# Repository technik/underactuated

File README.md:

# underactuated
Stuff related to the underactuated robotics class

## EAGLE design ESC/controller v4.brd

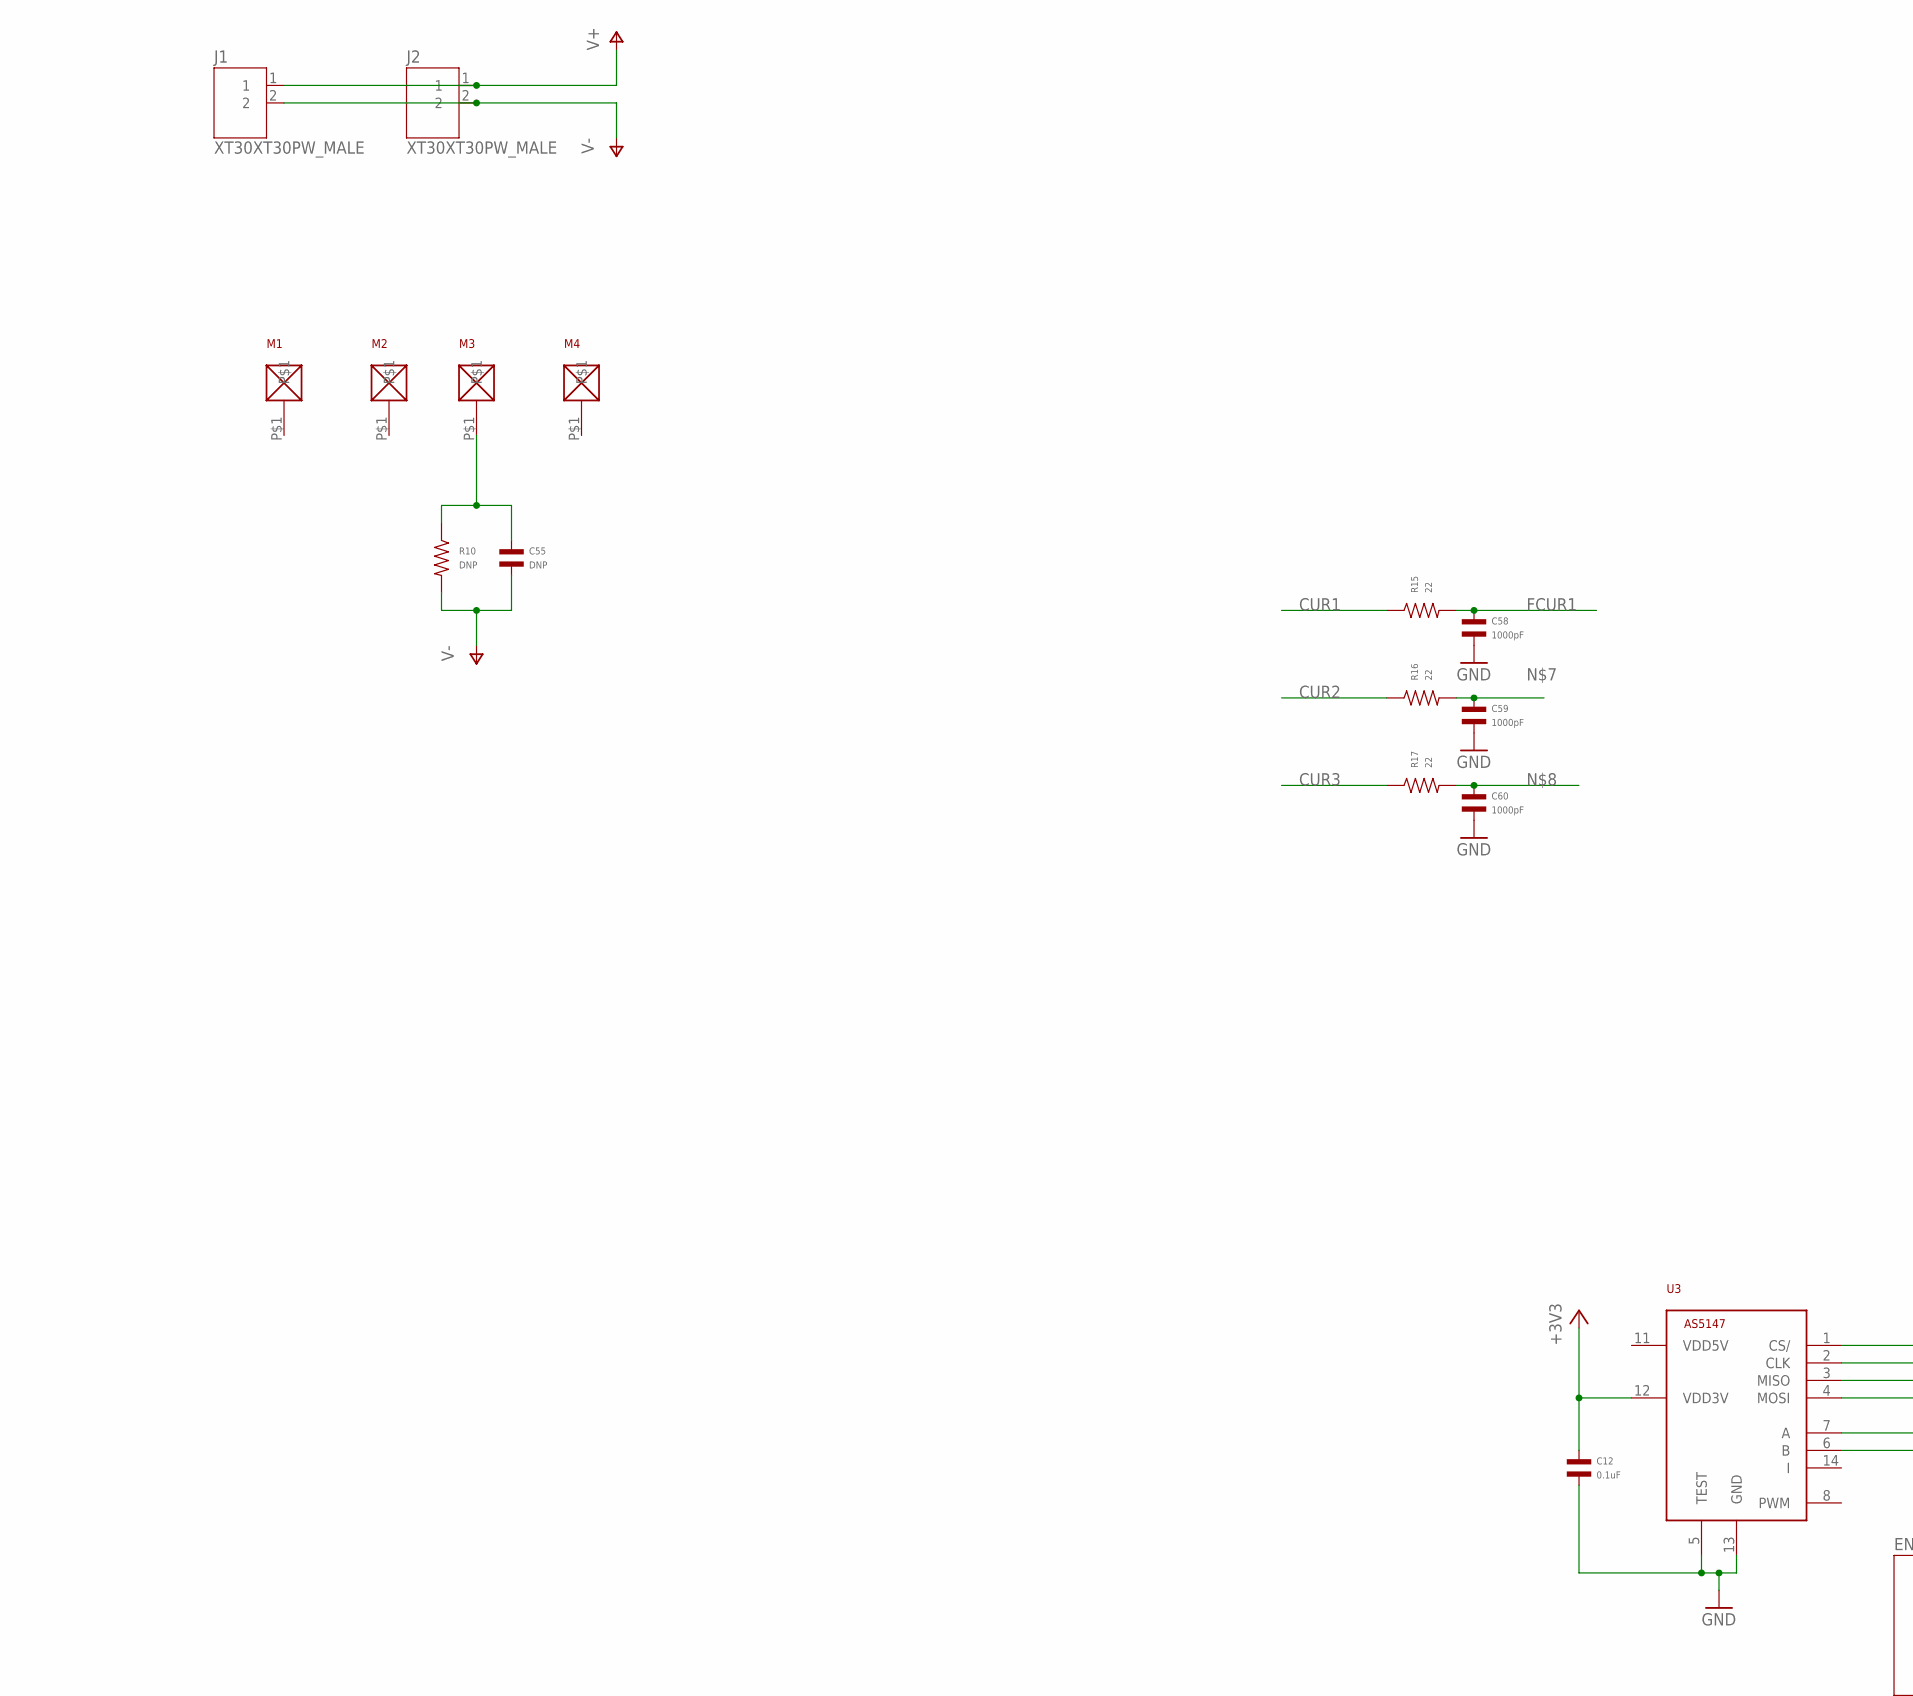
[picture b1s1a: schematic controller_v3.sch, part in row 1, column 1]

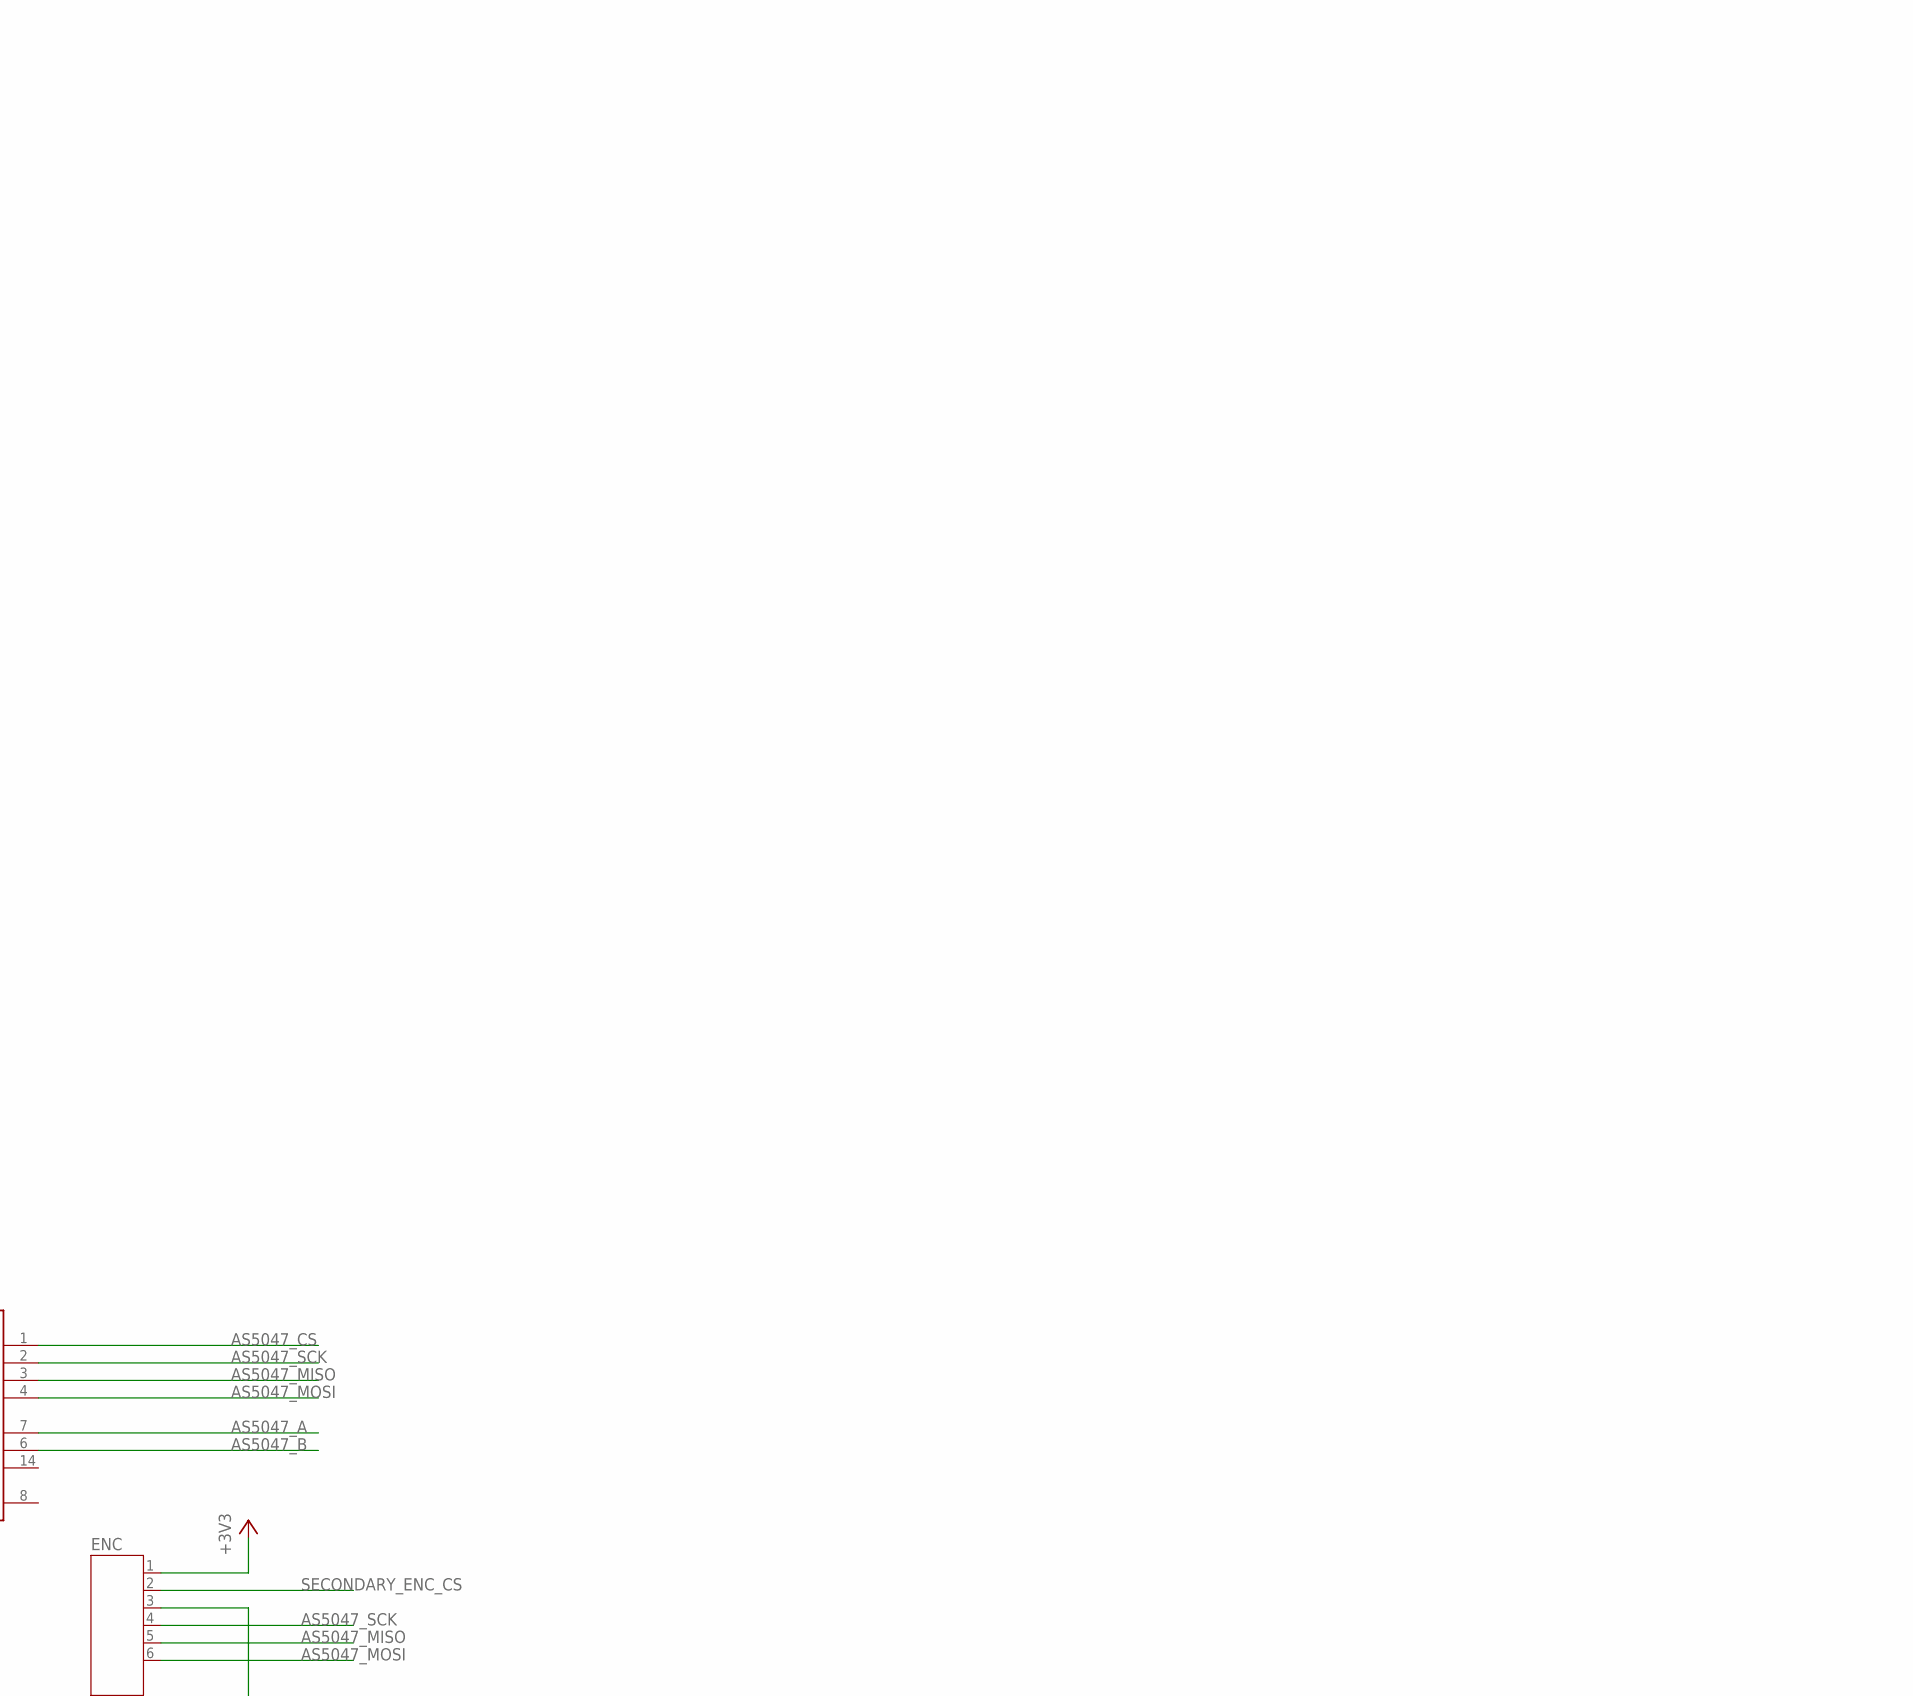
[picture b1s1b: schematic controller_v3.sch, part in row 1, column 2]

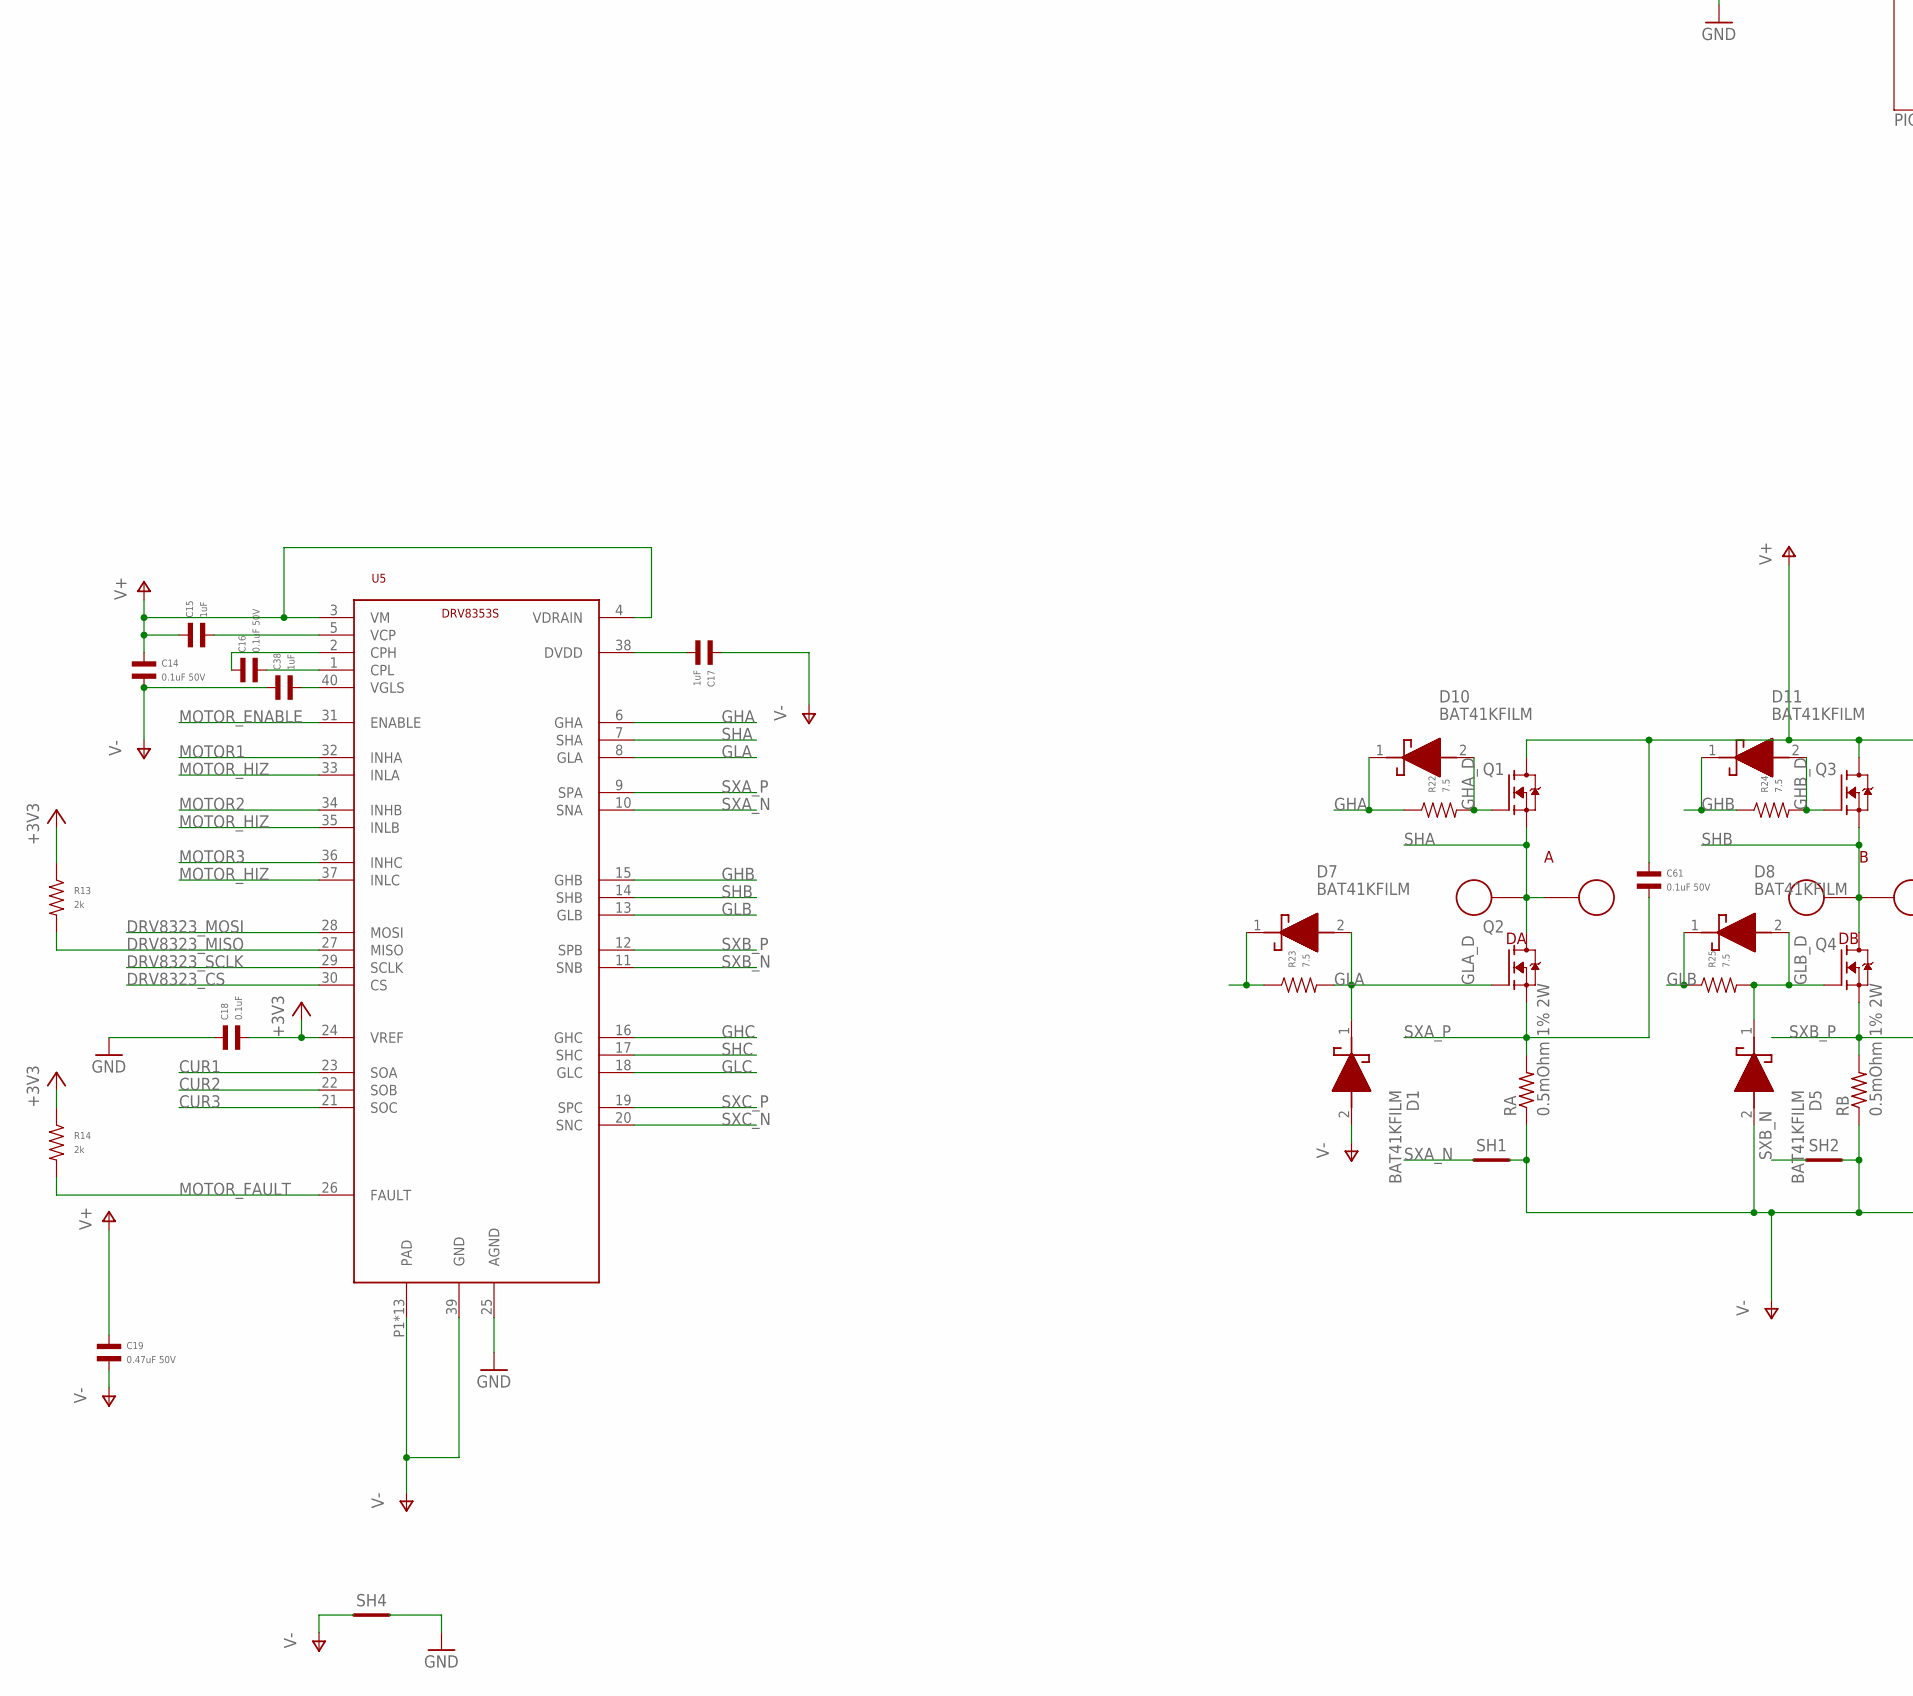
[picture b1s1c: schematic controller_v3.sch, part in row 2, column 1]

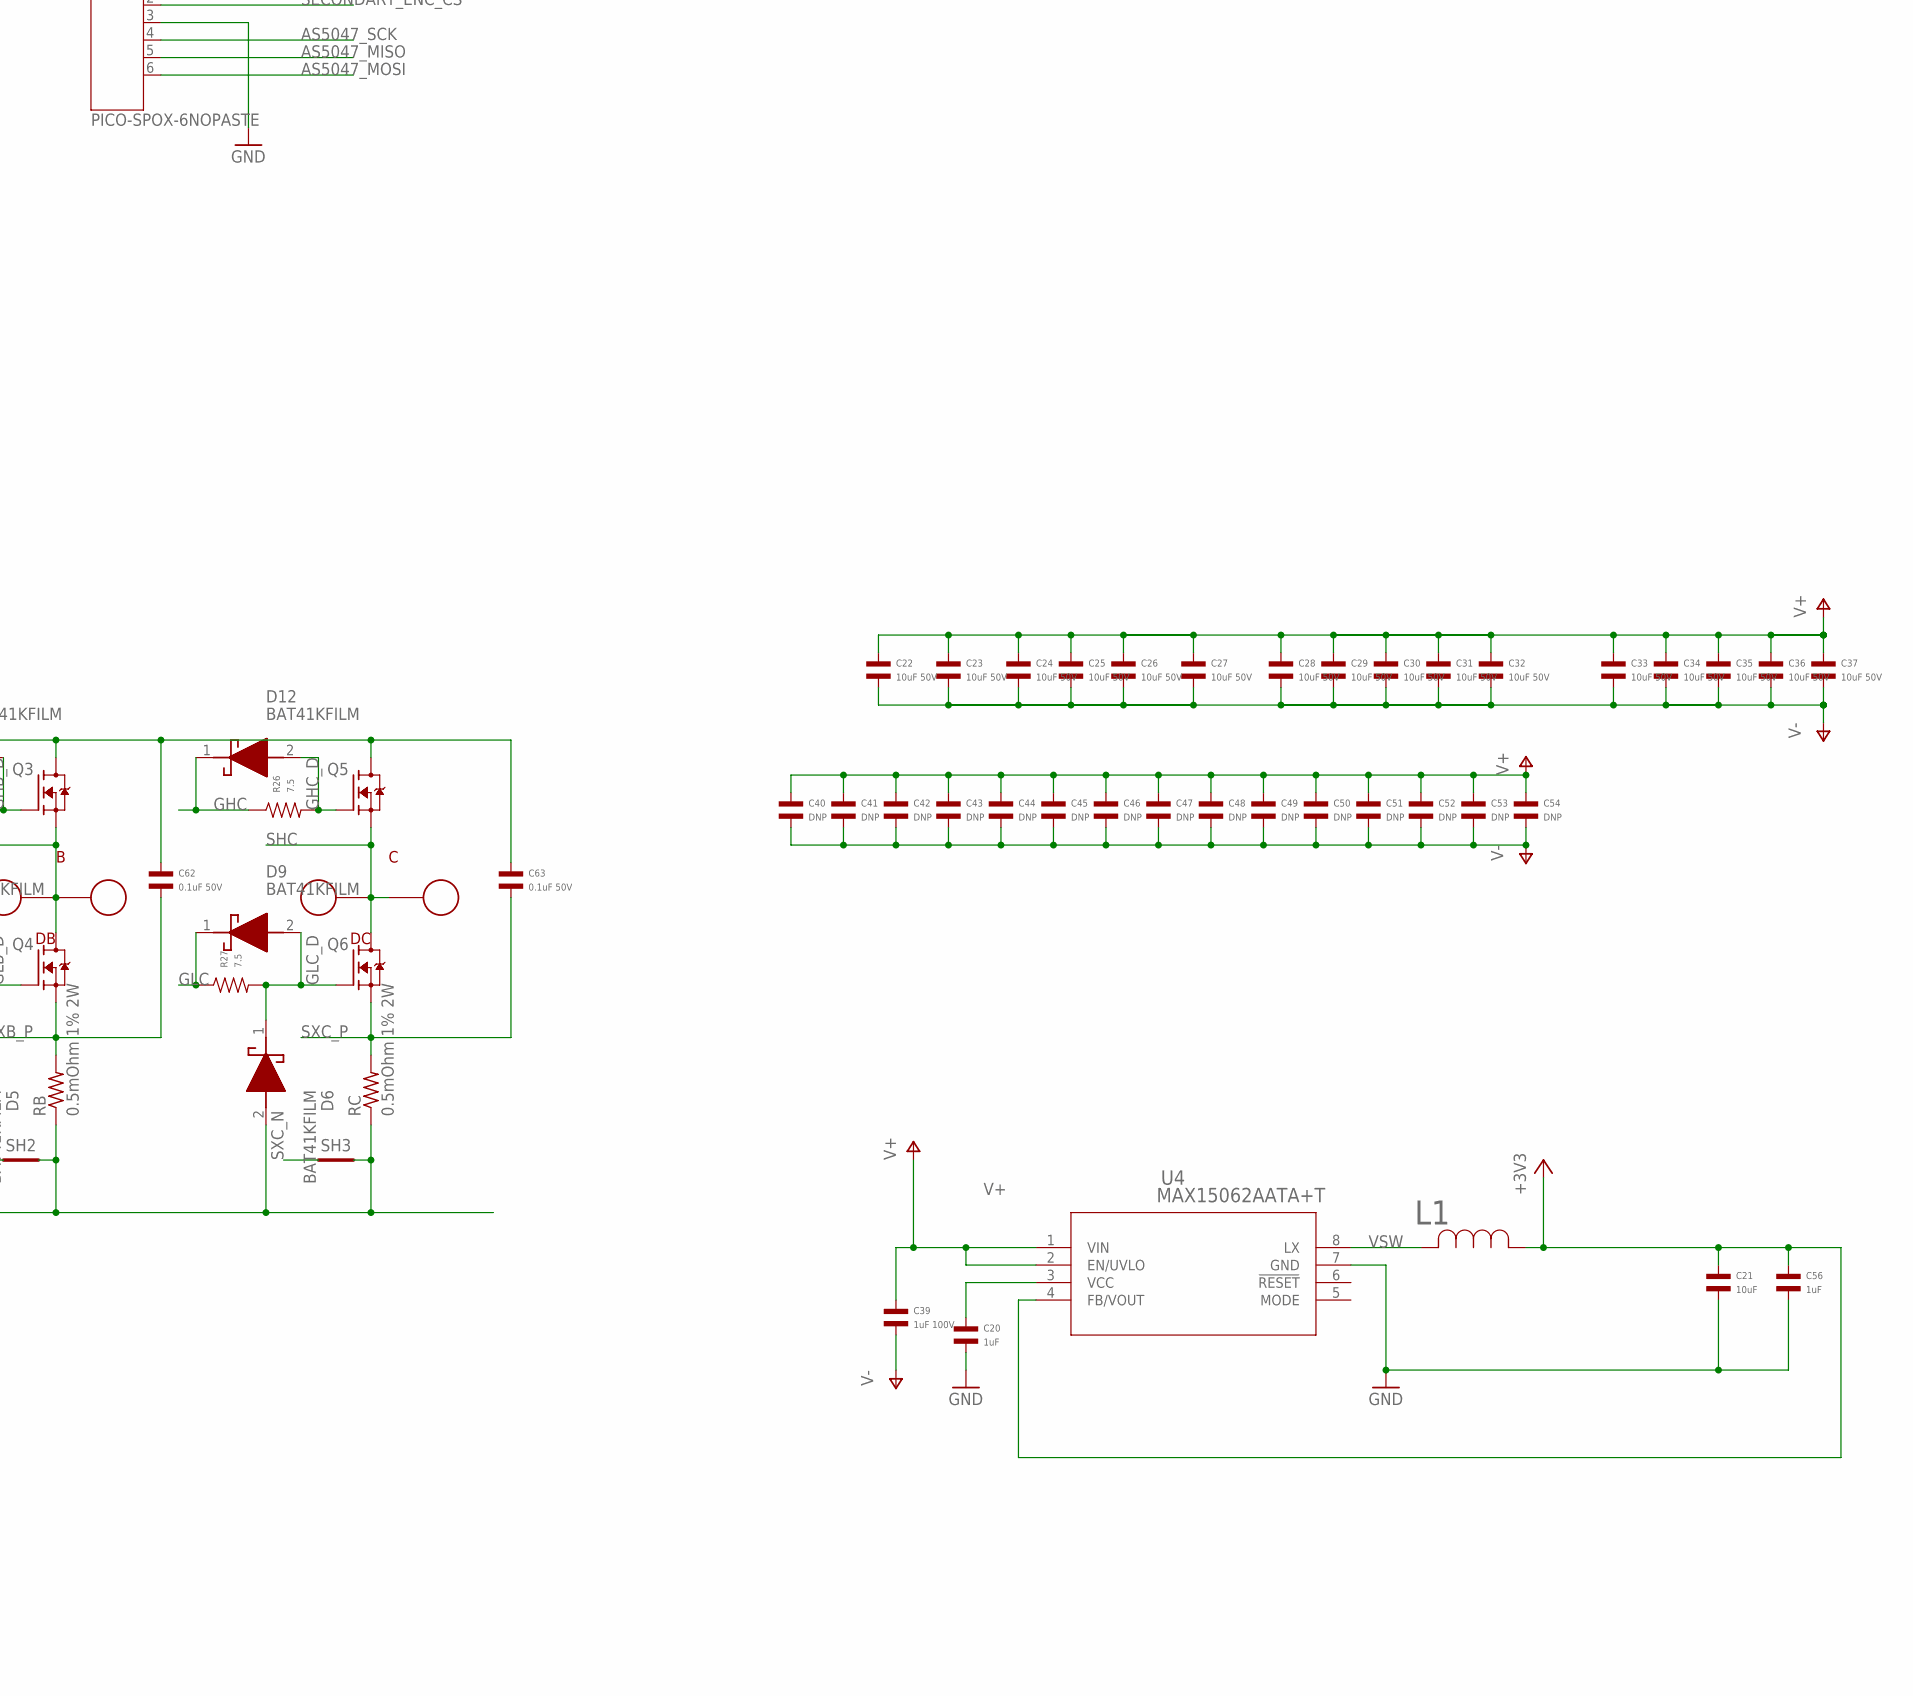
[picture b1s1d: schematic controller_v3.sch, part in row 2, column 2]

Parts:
A: PAD16AWG_PAD; 16AWG_PAD
B: PAD16AWG_PAD; 16AWG_PAD
C: PAD16AWG_PAD; 16AWG_PAD
C12, C18: 0.1uF; C0402; MPN MF-CAP-0402-0.1uF
C14, C16: 0.1uF 50V; C0402; MPN CGA2B3X7R1H104K050BB
C15, C17, C56: 1uF; C0402; MPN MF-CAP-0402-1uF
C19: 0.47uF 50V; C0402; MPN GRM155R61H474KE11D
C20: 1uF; C0603; MPN MF-CAP-0603-1uF
C21: 10uF; C1206; MPN MF-CAP-1206-10uF
C22, C23, C24, C25, C26, C27, C28, C29, C30, C31, C32, C33, C34, C36, C37: 10uF 50V; C1206; MPN C3216X7R1H106K160AE
C35: 10uF 50V; C1206_NOBORDER; MPN C3216X7R1H106K160AE
C38: 1uF; C0603; MPN C1608X7R1E105K080AE
C39: 1uF 100V; C0805; MPN GCM21BC72A105KE36L
C40, C41, C42, C43, C44, C45, C46, C47, C48, C49, C50, C51, C52, C53, C54: DNP; C1206_NOCREAM
C55: DNP; C0402
C58, C59, C60: 1000pF; C0402_NOBORDER; MPN MF-CAP-0402-1nF
C61, C63: 0.1uF 50V; C1206; MPN 12065C104KAZ2A
C62: 0.1uF 50V; C0603_NOBORDER; MPN 06035C104KAZ2A
D1, D5, D6, D7, D8, D9, D10, D11, D12: BAT41KFILM; SODFL1608X70N; MPN BAT41KFILM
DA: PAD24AWG_PAD; 24AWG_PAD
DB: PAD24AWG_PAD; 24AWG_PAD
DC: PAD24AWG_PAD; 24AWG_PAD
ENC: PICO-SPOX-6NOPASTE; PICO-SPOX-SMT-RA-6-NOPASTE
J1, J2: XT30XT30PW_MALE; XT30PW_MALE
L1: SRN4018-220M; IND_BOURNS_SRN4018; MANUFACTURER_PART_NUMBER SRN4018-330M
M1, M2, M3, M4: MOUNT; M2.5MOUNT
Q1, Q2, Q3, Q4, Q5, Q6: TPH1R204PLSOP_ADVANCE_8; SOP_ADVANCE_8; MPN TPH2R506PL,L1Q
R10: DNP; R0402
R13, R14: 2k; R0402; MPN MF-RES-0402-2K
R15, R16, R17: 22; R0402_NOBORDER; MPN MF-RES-0402-22
R22, R23, R24, R25, R26, R27: 7.5; R0402; MPN RC0402FR-077R5L
RA: 0.5mOhm 1% 2W; M1206; MPN HCS1206FTL500
RB: 0.5mOhm 1% 2W; M1206; MPN HCS1206FTL500
RC: 0.5mOhm 1% 2W; M1206; MPN HCS1206FTL500
SH1, SH2, SH3: SHORTT5; SHORT_TOP-50
SH4: SHORTMEDIUM; SHORT_TOP-MEDIUM
U3: AS5147; TSSOP14; MPN AS5047P-ATSM
U4: MAX15062AATA+T; 21-0487A_MXM; MPN MAX15062AATA+T
U5: DRV8353S; WQFN-40; MPN DRV8353FSRTAR

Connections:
+3V3: C12.P$1, C18.P$2, C21.P$1, C56.P$1, ENC.1, L1.1, R13.P$1, R14.P$1, U3.12 (VDD3V), U4.4 (FB/VOUT), U5.24 (VREF)
AS5047_A: U3.7 (A)
AS5047_B: U3.6 (B)
AS5047_CS: U3.1 (CS/)
AS5047_MISO: ENC.5, U3.3 (MISO)
AS5047_MOSI: ENC.6, U3.4 (MOSI)
AS5047_SCK: ENC.4, U3.2 (CLK)
CUR1: R15.P$1, U5.23 (SOA)
CUR2: R16.P$1, U5.22 (SOB)
CUR3: R17.P$1, U5.21 (SOC)
DRV8323_CS: U5.30 (CS)
DRV8323_MISO: R13.P$2, U5.27 (MISO)
DRV8323_MOSI: U5.28 (MOSI)
DRV8323_SCLK: U5.29 (SCLK)
FCUR1: C58.P$1, R15.P$2
GHA: D10.1 (K), R22.P$1, U5.6 (GHA)
GHA_D: D10.2 (A), Q1.4 (G), R22.P$2
GHB: D11.1 (K), R24.P$1, U5.15 (GHB)
GHB_D: D11.2 (A), Q3.4 (G), R24.P$2
GHC: D12.1 (K), R26.P$1, U5.16 (GHC)
GHC_D: D12.2 (A), Q5.4 (G), R26.P$2
GLA: D7.1 (K), R23.P$1, U5.8 (GLA)
GLA_D: D1.1 (K), D7.2 (A), Q2.4 (G), R23.P$2
GLB: D8.1 (K), R25.P$1, U5.13 (GLB)
GLB_D: D5.1 (K), D8.2 (A), Q4.4 (G), R25.P$2
GLC: D9.1 (K), R27.P$1, U5.18 (GLC)
GLC_D: D6.1 (K), D9.2 (A), Q6.4 (G), R27.P$2
GND: C12.P$2, C18.P$1, C20.P$2, C21.P$2, C56.P$2, C58.P$2, C59.P$2, C60.P$2, ENC.3, SH4.2, U3.5 (TEST), U3.13 (GND), U4.7 (GND), U5.25 (AGND)
MOTOR1: U5.32 (INHA)
MOTOR2: U5.34 (INHB)
MOTOR3: U5.36 (INHC)
MOTOR_ENABLE: U5.31 (ENABLE)
MOTOR_FAULT: R14.P$2, U5.26 (FAULT)
MOTOR_HIZ: U5.33 (INLA), U5.35 (INLB), U5.37 (INLC)
unnamed: C55.P$1, M3.P$1, R10.P$1
unnamed: C38.P$2, U5.40 (VGLS)
unnamed: C20.P$1, U4.3 (VCC)
unnamed: C59.P$1, R16.P$2
unnamed: C60.P$1, R17.P$2
unnamed: C16.P$2, U5.1 (CPL)
unnamed: C16.P$1, U5.2 (CPH)
unnamed: C15.P$2, U5.5 (VCP)
unnamed: C17.P$2, U5.38 (DVDD)
SECONDARY_ENC_CS: ENC.2
SHA: A.1, DA.P$1, Q1.1 (S), Q1.2 (S), Q1.3 (S), Q2.5 (D), Q2.6 (D), Q2.7 (D), Q2.8 (D), Q2.PAD (D), U5.7 (SHA)
SHB: B.1, DB.P$1, Q3.1 (S), Q3.2 (S), Q3.3 (S), Q4.5 (D), Q4.6 (D), Q4.7 (D), Q4.8 (D), Q4.PAD (D), U5.14 (SHB)
SHC: C.1, DC.P$1, Q5.1 (S), Q5.2 (S), Q5.3 (S), Q6.5 (D), Q6.6 (D), Q6.7 (D), Q6.8 (D), Q6.PAD (D), U5.17 (SHC)
SXA_N: SH1.1, U5.10 (SNA)
SXA_P: C61.P$2, Q2.1 (S), Q2.2 (S), Q2.3 (S), RA.2, U5.9 (SPA)
SXB_N: SH2.1, U5.11 (SNB)
SXB_P: C62.P$2, Q4.1 (S), Q4.2 (S), Q4.3 (S), RB.2, U5.12 (SPB)
SXC_N: SH3.1, U5.20 (SNC)
SXC_P: C63.P$2, Q6.1 (S), Q6.2 (S), Q6.3 (S), RC.2, U5.19 (SPC)
V+: C14.P$1, C15.P$1, C19.P$1, C22.P$1, C23.P$1, C24.P$1, C25.P$1, C26.P$1, C27.P$1, C28.P$1, C29.P$1, C30.P$1, C31.P$1, C32.P$1, C33.P$1, C34.P$1, C35.P$1, C36.P$1, C37.P$1, C39.P$1, C40.P$1, C41.P$1, C42.P$1, C43.P$1, C44.P$1, C45.P$1, C46.P$1, C47.P$1, C48.P$1, C49.P$1, C50.P$1, C51.P$1, C52.P$1, C53.P$1, C54.P$1, C61.P$1, C62.P$1, C63.P$1, J1.1, J2.1, Q1.5 (D), Q1.6 (D), Q1.7 (D), Q1.8 (D), Q1.PAD (D), Q3.5 (D), Q3.6 (D), Q3.7 (D), Q3.8 (D), Q3.PAD (D), Q5.5 (D), Q5.6 (D), Q5.7 (D), Q5.8 (D), Q5.PAD (D), U4.1 (VIN), U4.2 (EN/UVLO), U5.3 (VM), U5.4 (VDRAIN)
V-: C14.P$2, C17.P$1, C19.P$2, C22.P$2, C23.P$2, C24.P$2, C25.P$2, C26.P$2, C27.P$2, C28.P$2, C29.P$2, C30.P$2, C31.P$2, C32.P$2, C33.P$2, C34.P$2, C35.P$2, C36.P$2, C37.P$2, C38.P$1, C39.P$2, C40.P$2, C41.P$2, C42.P$2, C43.P$2, C44.P$2, C45.P$2, C46.P$2, C47.P$2, C48.P$2, C49.P$2, C50.P$2, C51.P$2, C52.P$2, C53.P$2, C54.P$2, C55.P$2, D1.2 (A), D5.2 (A), D6.2 (A), J1.2, J2.2, R10.P$2, RA.1, RB.1, RC.1, SH1.2, SH2.2, SH3.2, SH4.1, U5.39 (GND), U5.P1 (PAD), U5.P2 (PAD), U5.P3 (PAD), U5.P7 (PAD), U5.P8 (PAD), U5.P9 (PAD), U5.P12 (PAD), U5.P13 (PAD), U5.P14 (PAD), U5.P17 (PAD), U5.P18 (PAD), U5.P19 (PAD), U5.PAD
VSW: L1.2, U4.8 (LX)

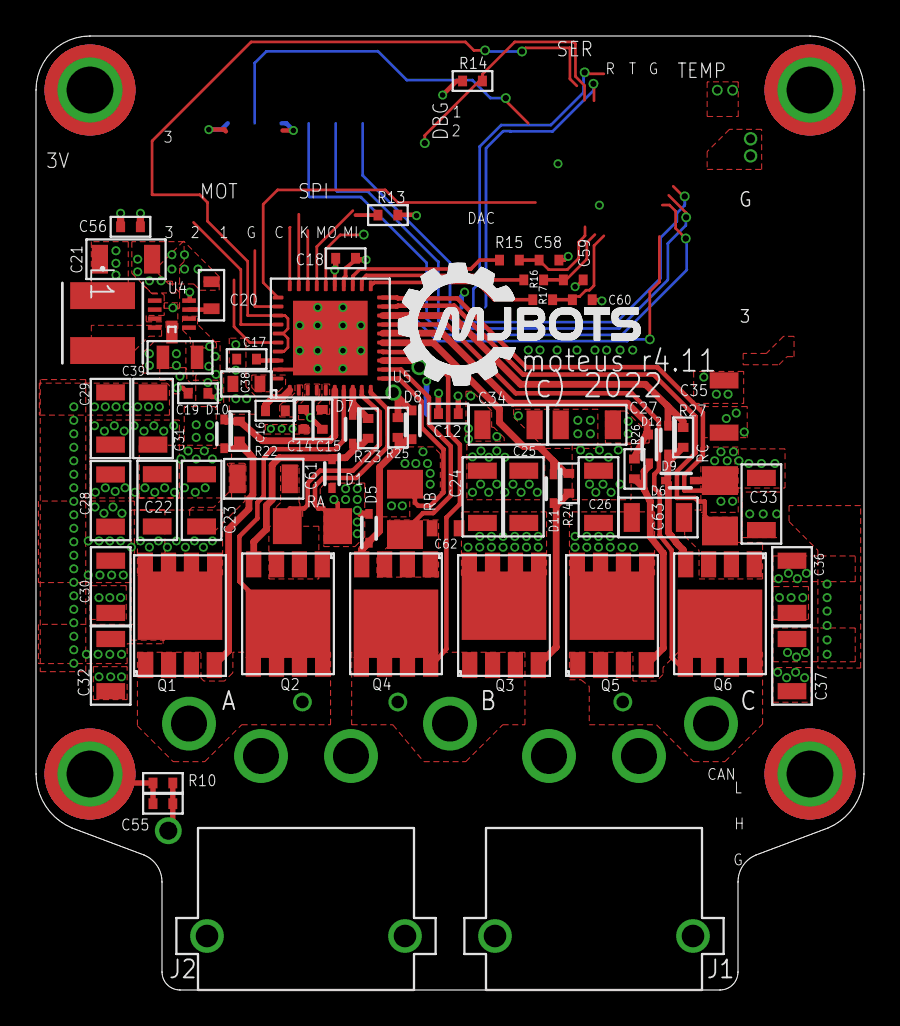
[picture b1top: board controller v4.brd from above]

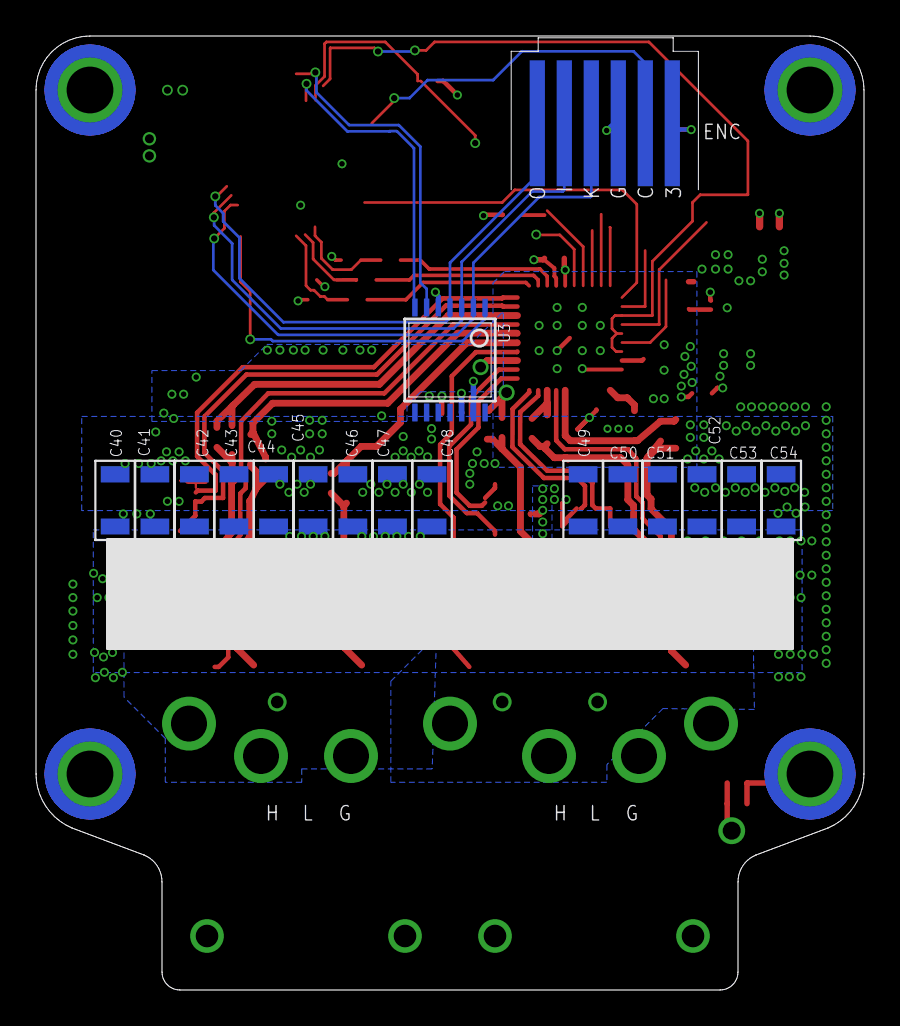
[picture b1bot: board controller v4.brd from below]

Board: 4 copper layers, 46.0 x 53.0 mm, 101 parts (17 on the bottom side), 45 nets.

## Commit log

2019-07-04 RobotHAL project
2019-07-04 Pendulum simulation
2023-02-18 Reorganize files and added an ImGui pendulum app
2023-02-18 Basic pendulum simulation
2023-02-18 Fixed numerical unstability
2023-02-18 randomize configurations
2023-02-18 Comment clean up
2023-02-18 better UI
2023-02-19 Energy pump controller for pendulum
2023-02-19 Setup acrobot project
2023-02-19 Acrobot: Use relative angles for the elbow.
2023-02-19 Mat22 implementation and WIP acrobot model
2023-02-20 WIP: Pendulum value iteration policy.
2023-02-25 WIP pendulum LQR and some more math ops
2023-02-25 Added dynamixel bridge project
2023-02-26 Add catkin workspace
2023-02-26 Update gitignore for ROS
2023-02-26 Fix CMake symlink
2023-02-26 Update CMake
2023-02-26 Add pendulum catkin pkg
2023-02-26 WIP Dynamixel bridge
2023-02-26 ROS skeleton of controller
2023-02-26 Upgrade to c++17
2023-02-26 Controller running in the controller node
2023-02-26 Controller in node (#1)
    * ROS skeleton of controller
    * Upgrade to c++17
    * Controller running in the controller node
2023-02-26 LED toggle and WIP reading from PC
2023-02-26 Add Pendulum urdf and rviz launch files
2023-02-26 pass on dynamixel bridge
2023-02-26 Refactor: Make a folder for each node in the pendulum package
2023-02-27 WIP pendulum sim node
2023-03-01 Uncomment simulation
2023-03-01 Remove devel
2023-03-01 pendulum simulator subscibes to the control topic.
2023-03-01 Added serial port library for linux
2023-03-07 4th order Runge-Kutta simulation
2023-03-07 Add control input subscriber
2023-03-08 Add matplotlib-based visualizer
2023-03-08 Add PD to controller
2023-03-08 Cleanup
2023-03-08 Add energy plot
2023-03-09 Fix typo g=9.18 🙄
2023-03-09 remove const value param
2023-03-09 HAL Updates
2023-03-09 Add ros_lib
2023-03-11 Clean up build folder (shouldn't be tracked)
2023-03-11 Multiplatform implementation of serial port
2023-03-11 Hal serial port (#5)
    * Added serial port library for linux
    * Clean up build folder (shouldn't be tracked)
    * Multiplatform implementation of serial port
2023-03-11 Dynamixel writes
2023-03-12 WIP: Extending dynamixel functionality
2023-03-13 wip hal
2023-03-13 wip read data from ax12
2023-03-13 Build fix
2023-03-13 Ping dynamixel AX12
2023-03-24 Arduino motor controller
2023-03-25 Working?
2023-03-25 WORKING!
2023-03-25 Cleanup prints
2023-03-26 Improved half bridge dynamixel control
2023-03-27 Refactoring
2023-03-27 Working bang-bang energy shaping controll
2023-03-27 Fix date
2023-04-08 Hopper v2 test code
2023-04-08 bldc motor moves in both directions
2023-04-09 First version of Field oriented Control
2023-04-10 Faster trapezoidal control
2023-05-24 Hopper cube local changes
2023-06-01 Add a micromouse project and share some code
2023-06-30 Add clean ESC
2023-09-23 rattrap gyro
2023-09-27 WIP: Test code for esc_v5
2023-10-02 working h-bridge on the esc
2023-10-02 Added a segway model using the Arduino framework on the stm32 nucleo F446re
2023-10-02 clean code and add a can library to the project
2023-10-17 missing segway code
2023-10-18 Wheeled pendulum EoM
2023-10-19 Wheeled pendulum EoM (#7)
2023-10-22 Segway project: WIP rigid body simulation
2023-10-22 Moved rendering into a presentation class
2023-10-23 circle to circle collision detection
2023-10-23 Introducing AABBs
2023-10-23 circle to box intersection
2023-10-27 force generators
2023-10-27 support kinematic bodies
2023-10-28 Basic pivot constraint
2023-10-28 WIP: Big matrix for the constraint solver
2023-10-29 Removed custom matrix code
2023-11-20 RK4 Segway simulator
2024-02-27 EKF in python
2024-03-10 Noisy signal EKF test
2024-03-16 copied pendulum mode into a new project folder
2024-03-16 Differential cart model
2024-03-17 cart simulation
2024-03-17 added eigen and implemented a linear actuation policy
2024-03-17 add a timeout
2024-03-17 Compute a score for each run
2024-03-17 WIP training
2024-03-17 Training works on debug, but not release
2024-03-17 fix stack corruption that was breaking training.
2024-03-17 update default training configuration.
2024-03-18 Draw network activations
2024-03-21 multilayer perceptron working
2024-03-21 local search training
2024-03-21 policy now controls motor velocity directly (simplified problem).
2024-03-21 stochastic gradient descent
2024-03-22 better viz + sgd controls
2024-03-22 refactored simulation out of main app class
2024-03-22 reward time
2024-03-23 train across the whole track, on a predefined set of test cases
2024-03-23 SGD magnitude fix
2024-03-23 Added sin/cos to the MLP policy. It now learns more complex trajectories.
2024-03-23 WIP: Multisegment track
2024-03-24 WIP: segmented track
2024-03-24 cmake clean ups
2024-03-24 Further cmake refactoring
2024-03-25 WIP: Implementation of fully connected NN blocks
2024-03-25 NN fixes
2024-03-25 using NN model inside MLP policy
2024-03-25 removed unnecessary inputs from the model
2024-03-25 successful training on the multisegment track
2025-02-18 real time clock
2025-02-18 tracks can now be overriden
2025-02-18 a few notes and references

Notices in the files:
ESC/controller v4.brd:
(c) 2022
ESC/controller_v3.sch:
Licensed under the Apache 2.0 License
parts and their libraries:
COPYRIGHT: Copyright (C) 2018 Accelerated Designs. All rights reserved
